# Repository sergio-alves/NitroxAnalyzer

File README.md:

# NitroxAnalyzer
This repository contains everything needed to build a nitrox analyzer that uses a compatible R17 O2 cell and that connects to a mobile phone running on Android.

The finished product:

Read [the wiki page](https://github.com/sergio-alves/NitroxAnalyzer/wiki) to get more information about the project.

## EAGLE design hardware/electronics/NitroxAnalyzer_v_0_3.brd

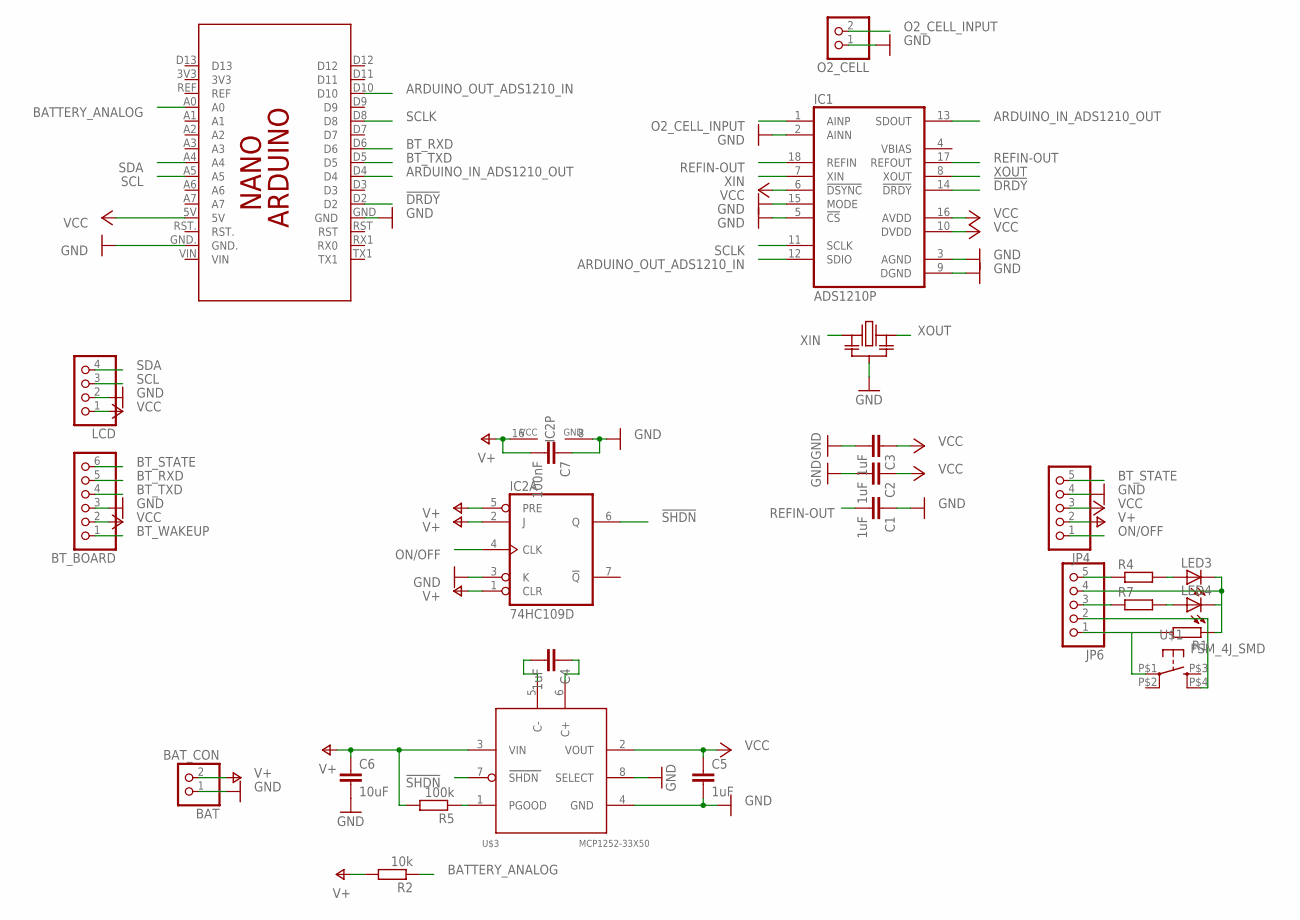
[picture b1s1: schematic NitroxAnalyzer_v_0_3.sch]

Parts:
BAT: BAT_CON; 1X02
BT_BOARD: PINHD-1X6; 1X06
C1, C2, C3, C4, C5: 1uF; C1206
C6: 10uF; C1206
C7: 100nF; C1206
IC1: ADS1210P; DIL18
IC2: 74HC109D; SO16
JP4: PINHD-1X5; 1X05
JP6: PINHD-1X5/90; 1X05/90
LCD: PINHD-1X4; 1X04
LED3, LED4: LEDSML0805; SML0805
O2_CELL: PINHD-1X2; 1X02
PCB1: ARDUINO_NANO_SOCKET
R1, R4, R7: R-EU_R1206; R1206
R2: 10k; R1206
R5: 100k; R1206
U$1: FSM_4J_SMD; B3F-10XX
U$2: RESONATOR
U$3: MCP1252-33X50; MSOP8

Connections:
!DRDY: IC1.14 (!DRDY), PCB1.D2
!SHDN: IC2.6 (Q), U$3.7 (SHDN)
ARDUINO_IN_ADS1210_OUT: IC1.13 (SDOUT), PCB1.D4
ARDUINO_OUT_ADS1210_IN: IC1.12 (SDIO), PCB1.D10
BATTERY_ANALOG: PCB1.A0, R2.1
BT_RXD: BT_BOARD.5, PCB1.D6
BT_STATE: BT_BOARD.6, JP4.5
BT_TXD: BT_BOARD.4, PCB1.D5
BT_WAKEUP: BT_BOARD.1
GND: BAT.1, BT_BOARD.3, C1.1, C2.2, C3.2, C5.2, C6.2, C7.1, IC1.2 (AINN), IC1.3 (AGND), IC1.5 (!CS), IC1.9 (DGND), IC1.15 (MODE), IC2.3 (K), IC2.8 (GND), JP4.4, LCD.2, O2_CELL.1, PCB1.GND, PCB1.GND., U$2.P$2 (GND), U$3.4 (GND), U$3.8 (SELECT)
unnamed: C4.1, U$3.6 (C+)
unnamed: R5.1, U$3.1 (PGOOD)
unnamed: LED3.A, R4.2
unnamed: LED4.A, R7.2
unnamed: C4.2, U$3.5 (C-)
O2_CELL_INPUT: IC1.1 (AINP), O2_CELL.2
ON/OFF: IC2.4 (CLK), JP4.1
REFIN-OUT: C1.2, IC1.17 (REFOUT), IC1.18 (REFIN)
SCL: LCD.3, PCB1.A5
SCLK: IC1.11 (SCLK), PCB1.D8
SDA: LCD.4, PCB1.A4
V+: BAT.2, C6.1, C7.2, IC2.1 (CLR), IC2.2 (J), IC2.5 (PRE), IC2.16 (VCC), JP4.2, R2.2, R5.2, U$3.3 (VIN)
VCC: BT_BOARD.2, C2.1, C3.1, C5.1, IC1.6 (!DSYNC), IC1.10 (DVDD), IC1.16 (AVDD), JP4.3, LCD.1, PCB1.5V, U$3.2 (VOUT)
XIN: IC1.7 (XIN), U$2.P$1 (IN)
XOUT: IC1.8 (XOUT), U$2.P$3 (OUT)
_BT_STATE: JP6.5, R4.1
_ON_OFF: JP6.1, R1.2, U$1.P$1
_V+: JP6.2, U$1.P$4 (S1)
_VCC: JP6.3, R7.1
__GND: JP6.4, LED3.C, LED4.C, R1.1

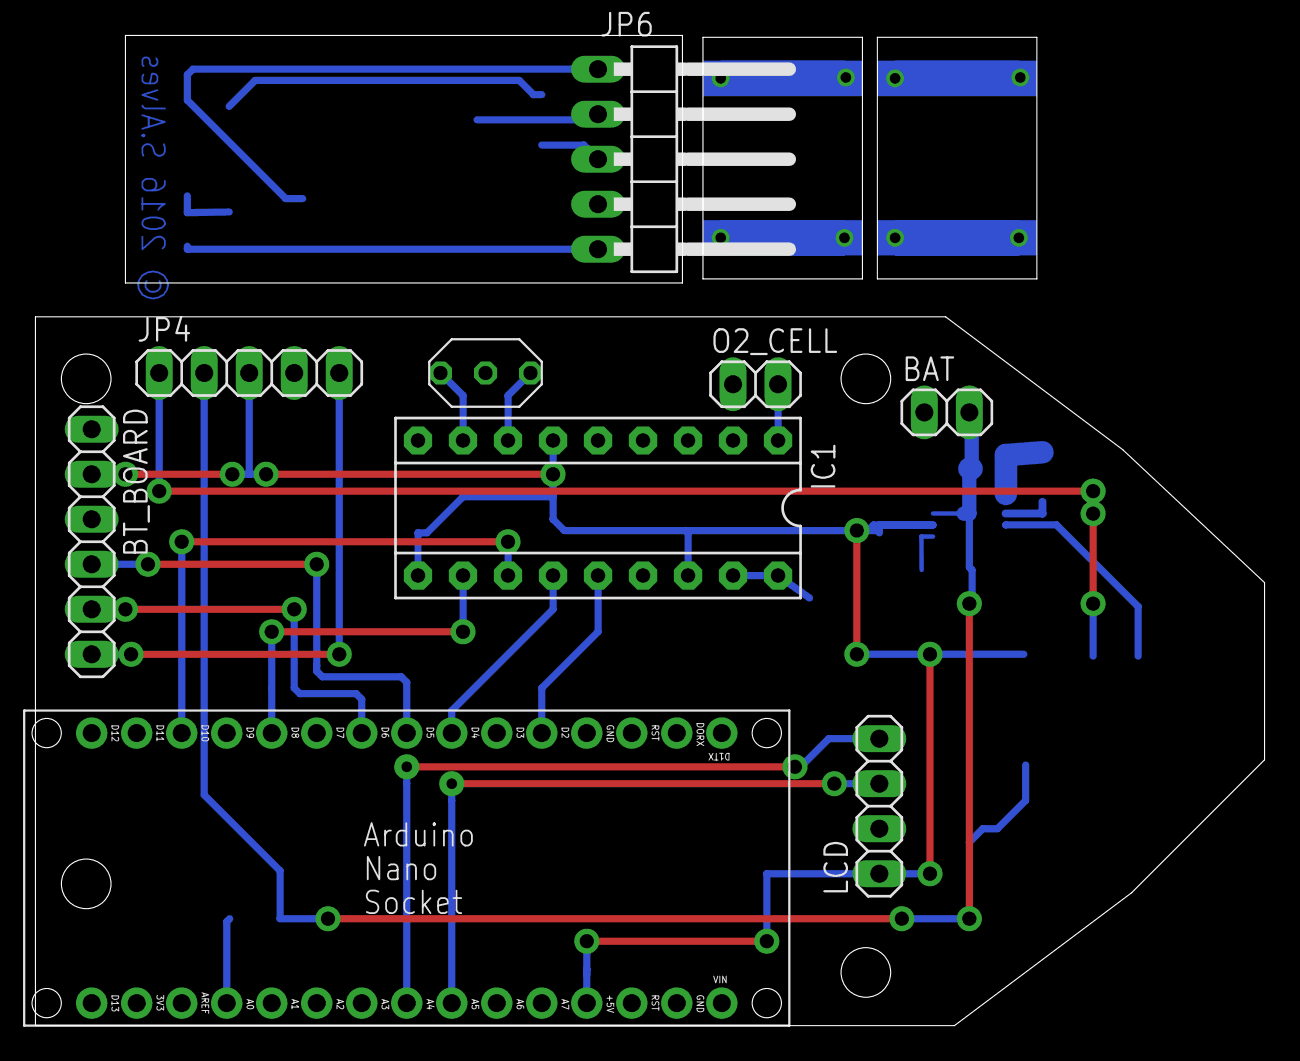
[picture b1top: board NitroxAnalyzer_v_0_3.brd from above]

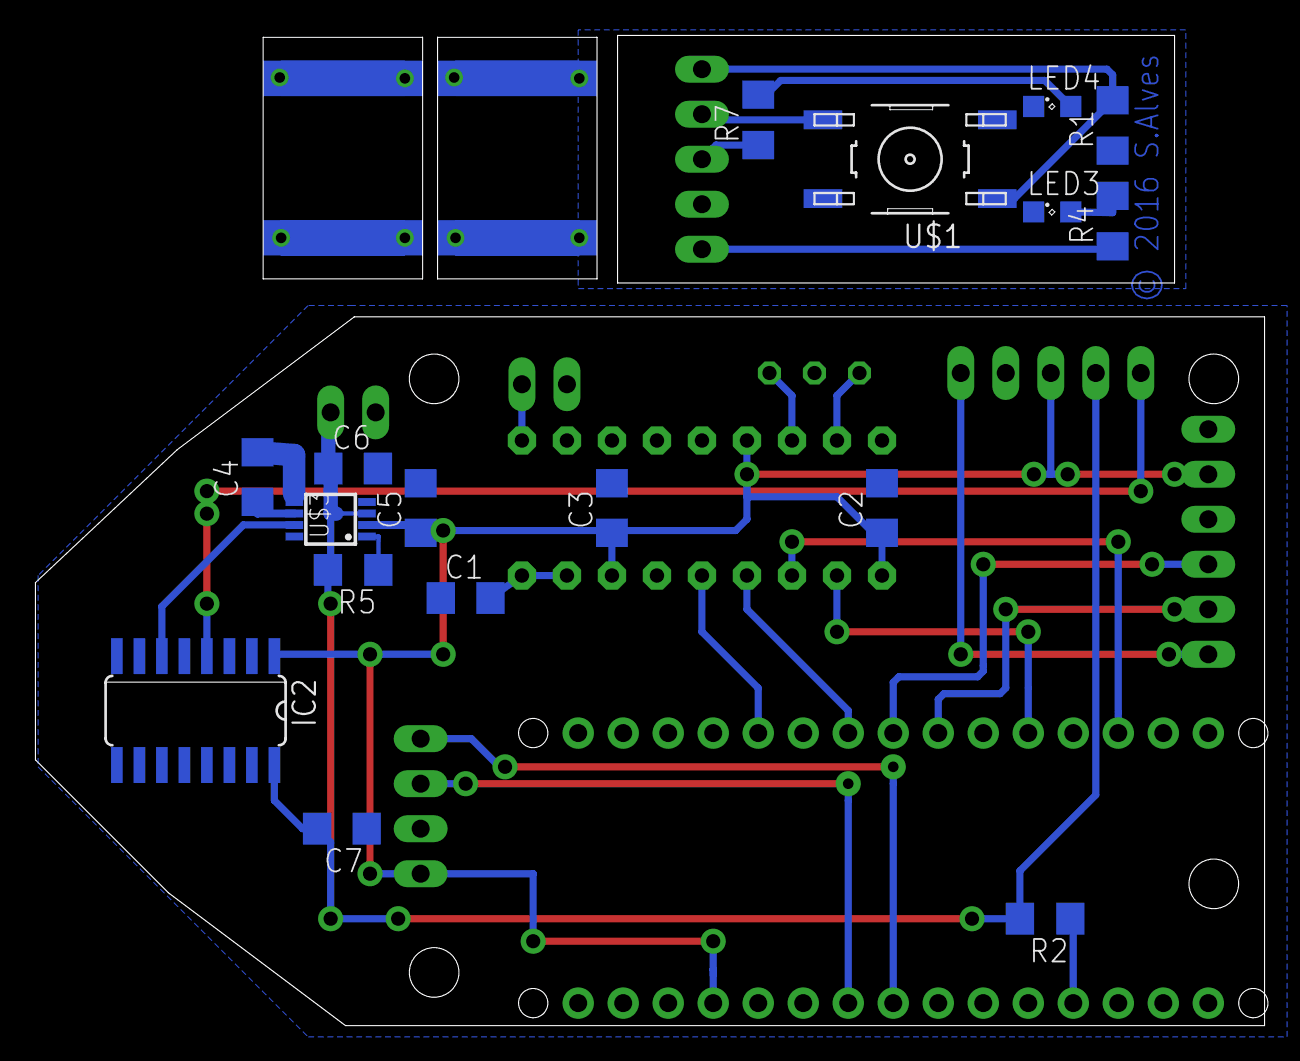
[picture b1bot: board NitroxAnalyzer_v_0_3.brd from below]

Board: 2 copper layers, 69.4 x 55.9 mm, 26 parts (17 on the bottom side), 29 nets.

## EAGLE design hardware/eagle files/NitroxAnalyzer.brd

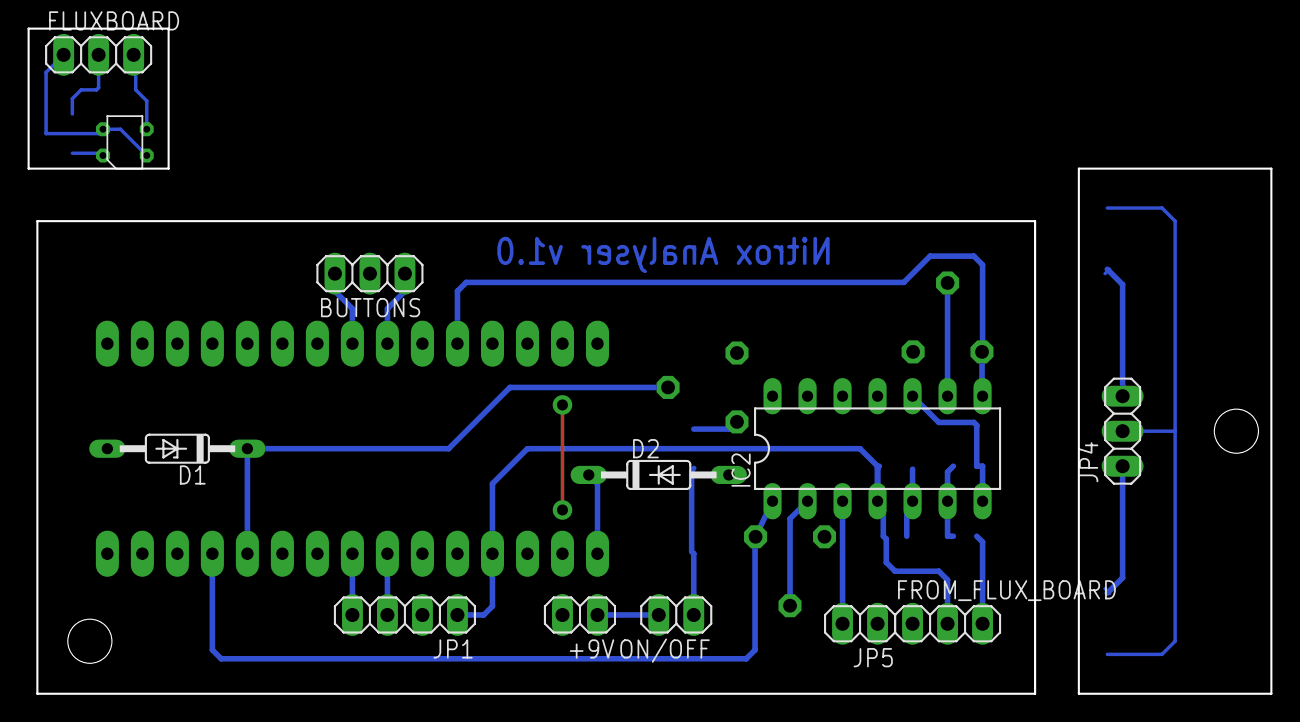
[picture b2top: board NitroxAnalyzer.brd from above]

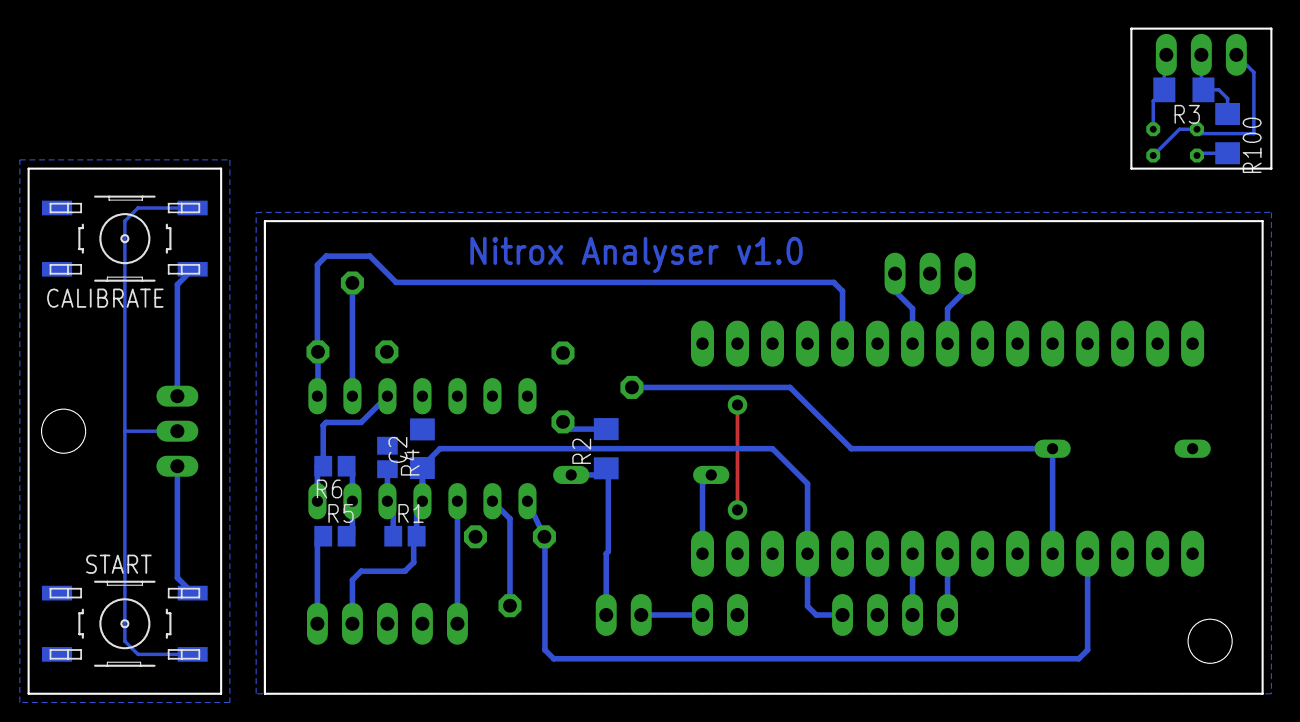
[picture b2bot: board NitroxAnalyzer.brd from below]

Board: 2 copper layers, 90.2 x 48.3 mm, 26 parts (10 on the bottom side), 27 nets.

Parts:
+9V: BAT_CON; 1X02
BUTTONS: 1X03
C2: 100n; C1206
CALIBRATE: FSM_4J_SMD; B3F-10XX
D1: BZX55; DO35Z10
D2: BA221; DO35-10
FLUXBOARD: 1X03
FROM_FLUX_BOARD: 1X03
IC2: LM2902N; DIL14
JP1: OLED_CON; 1X04
JP4: BUTTON_CON@2; 1X03
JP5: O2_CELL_CON; 1X02
ON/OFF: BAT_CON; 1X02
R1, R4, R5, R6: 91K; R0805
R2: 6K; R1206
R3: 10K; R1206
R100: 220; R1206
START: FSM_4J_SMD; B3F-10XX
U$1: 10K; PT6KV
U$2, U$5: 100K; PT6KV
U$3: 4PIN
U$4: DIL30

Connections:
+9V: D2.A, ON/OFF.1, R2.1
BATTERY_ANALOG: D1.C, U$1.C, U$4.P$20
CALIBRATE: BUTTONS.3, U$4.P$8
FLUX_DIGITAL: IC2.8, U$4.P$5, U$5.B
GND: +9V.2, BUTTONS.2, C2.2, D1.A, FROM_FLUX_BOARD.1, IC2.11, JP1.2, JP5.1, R4.1, U$1.B, U$2.A, U$4.P$4, U$4.P$29, U$5.A
GND_: FLUXBOARD.1, U$3.C, U$3.EMI
unnamed: R100.2, U$3.A
unnamed: IC2.2, U$2.C
unnamed: CALIBRATE.P$1, JP4.3
unnamed: +9V.1, ON/OFF.2
unnamed: JP4.1, START.P$2
unnamed: CALIBRATE.P$3, JP4.2, START.P$4
unnamed: D2.C, U$4.P$30
unnamed: R2.2, U$1.A
unnamed: IC2.7, IC2.10, R6.2
unnamed: IC2.6, R5.2, R6.1
unnamed: FROM_FLUX_BOARD.3, R5.1
unnamed: IC2.5, R1.1, R4.2
unnamed: IC2.9, U$5.C
unnamed: IC2.3, JP5.2
O2_CELL_ANALOG: IC2.1, U$2.B, U$4.P$19
SCL: JP1.3, U$4.P$24
SDA: JP1.4, U$4.P$23
SIG: FLUXBOARD.3, R3.2, U$3.COL
START: BUTTONS.1, U$4.P$7
VCC: C2.1, FROM_FLUX_BOARD.2, IC2.4, JP1.1, R1.2, U$4.P$27
VCC_: FLUXBOARD.2, R3.1, R100.1

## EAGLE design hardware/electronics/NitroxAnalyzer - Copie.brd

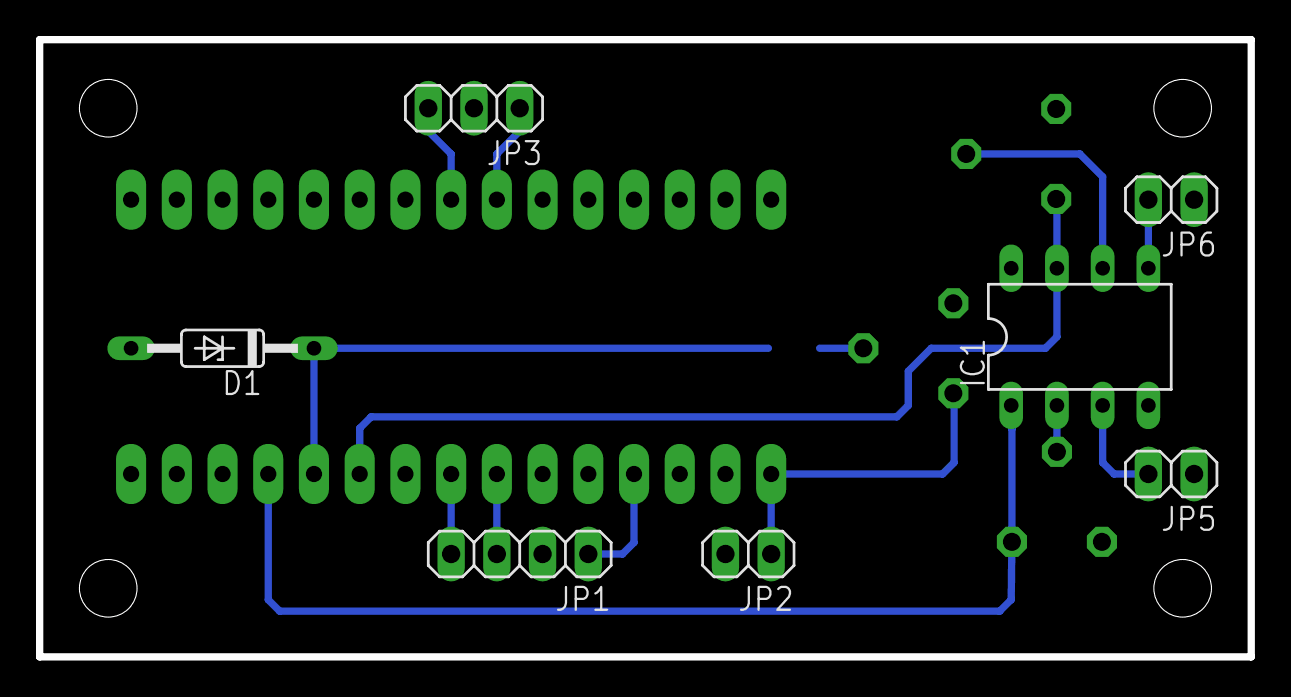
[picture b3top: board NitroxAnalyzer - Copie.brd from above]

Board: 2 copper layers, 67.3 x 34.3 mm, 12 parts (1 on the bottom side), 15 nets.

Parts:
D1: BZX55; DO35Z10
IC1: DIL08
JP1: OLED_CON; 1X04
JP2: BAT_CON; 1X02
JP3: BUTTONS_CON@1; 1X03
JP5: O2_CELL_CON; 1X02
JP6: FLUX_SENSOR_CON; 1X02
R1: 10k; R1206
U$1, U$2, U$3: PT6KV-10k; PT6KV
U$4: DIL30

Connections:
+9V: JP2.1, U$1.A, U$4.P$30
BATTERY_ANALOG: D1.C, R1.2, U$4.P$20
CALIBRATE: JP3.3, U$4.P$8
FLUX_ANALOG: IC1.7, U$3.A, U$4.P$21
FLUX_SIGNAL: IC1.5, JP6.2
GND: D1.A, JP1.2, JP2.2, JP3.2, JP5.1, JP6.1, U$1.B, U$2.B, U$3.B, U$4.P$4, U$4.P$29
unnamed: R1.1, U$1.C
unnamed: IC1.2, U$2.C
unnamed: IC1.6, U$3.C
O2_CELL_ANALOG: IC1.1, U$2.A, U$4.P$19
O2_SIGNAL: IC1.3, JP5.2
SCL: JP1.3, U$4.P$24
SDA: JP1.4, U$4.P$23
START: JP3.1, U$4.P$7
VCC: JP1.1, U$4.P$27

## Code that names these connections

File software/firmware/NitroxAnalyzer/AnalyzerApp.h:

#pragma once

#include <Arduino.h>
#include <EEPROM.h>
#include <SoftwareSerial.h>
#include <EEPROM.h>
#include <Wire.h>
#include <OzOLED.h>
#include "ADS1210Driver.h"
#include "OzOledDisplayAdapter.h"
#include "SerialProtocolHandler.h"
#include "Averager.h"


/*
enum ApplicationStates {

autoCalibrateAction,
autoMesuringAction,
refreshBatteryState,
refreshDataInOutState,
refreshBluetoothState,
displayBTConnectedScreen,
getBatteryLoad,
setO2CellInstallDate,
setO2CellValidityDate,
STATE_IDLE,
STATE_EXECUTE_GET_AVERAGE_INIT,
STATE_EXECUTE_GET_AVERAGE_READ_VALUES,
STATE_EXECUTE_GET_AVERAGE_RETURN_RESPONSE,
STATE_EXECUTE_GET_BATTERY_LOAD,
STATE_EXECUTE_GET_O2_CELL_INSTALL_DATE,
STATE_EXECUTE_SET_O2_CELL_INSTALL_DATE,
DISPLAY_SCREEN_ICONS,
};








*/

//----------------------------------------------------------------------------------------------------------
// Externals -----------------------------------------------------------------------------------------------
//----------------------------------------------------------------------------------------------------------
extern void adcIRQ();
class AnalyzerApp;

//----------------------------------------------------------------------------------------------------------
// Definitions ---------------------------------------------------------------------------------------------
//----------------------------------------------------------------------------------------------------------

#define isEEPROMClean() eeprom.configuration.clean==0xCAFEBABE

// pins related 

#define BATTERY_ANALOG_PIN				A0

#define ADS1210_CLK						8
#define ARDUINO_OUT_ADS1210_IN			10
#define ARDUINO_IN_ADS1210_OUT			4


//buttons related
#define LEFT_BUTTON						11
#define RIGHT_BUTTON					12

#define DEBOUNCE_MAX_MS					20

typedef struct {
	unsigned long lastUpdate;
	int currentState;
	void(AnalyzerApp::*onPush)(int);
	void(AnalyzerApp::*onRelease)(int);
	void(AnalyzerApp::*onPressed)(int, int);
} ButtonState;


// counters related
#define COUNTERS_SIZE					4

enum  Counters {
	mainCounter,
	bluetoothIcon,
	inOutCounter,
	bluetoothConnectionAlive,
};


//eeprom related 
#define EEPROM_STORED_DATA_SIZE			12
#define EEPROM_CONFIG_START_ADDRESS		0

typedef struct {
	int day;
	int month;
	int year;
} date;

typedef struct {
	long clean;
	struct {
		date install_date; //6 bytes
		date change_date;  //6 bytes
	} O2Cell; // 12 bytes
} AnalyzerConfiguration;

typedef union {
	byte data[sizeof(AnalyzerConfiguration)];
	AnalyzerConfiguration configuration;
} EEPROMContent;

//communication speed related
#define SOFTWARE_RX_PIN					5
#define SOFTWARE_TX_PIN					6

#define SERIAL_BAUDRATE					115200
#define BLUETOOTH_BAUDRATE				9600


// screens and loops related
#define SPLASH_SCREEN_DURATION_MS		2000

enum ScreenLoop {
	SplashScreen,
	ManualScreen,
	BluetoothScreen,
};
enum ApplicationStates {
	idle,
	wait,
	calibrate,
	measure,
	displaySplashScreen,
	displayMainScreen,

	getO2CellInstallDate,
	getO2CellValidityDate,
};

enum DataInOutState{
	none,
	in,
	out,
	inout,
};

/* Calibration related */
#define CALIBRATION_MAX_ITERATIONS  100
#define O2_READ_ITERATIONS			10


/* Class to handle the analyzer application.
   Calibration and measures can be done using the box or through the bt interface (if available)
   then the structure must be rather flexible.
   On BT Connection device will answer to bt commands only, no device interaction possible. */
class AnalyzerApp
{
public:
	void doLoop();
	void doSetup();
	inline void setNewADCValueAvailable(bool val) { newADCValueAvailable = val; }

protected:
	/* button events related functions */
	void onButtonPressed(int btnId, int length);
	void onButtonRelease(int btnId);
	void onButtonPush(int btnId);
	void poolButtonsState();
	bool stateChangedDebounced(int);

	/* sub loops related */
	ScreenLoop splashScreenLoop();
	ScreenLoop manualScreenLoop();
	ScreenLoop bluetoothScreenLoop();

	/* displaying related*/
	void drawsManualMainScreen();
	int getBatteryPercent();
	int getBatteryMappedValue();
	void inOutIconUpdate(bool send, bool receive);
	void convertDecimalToDigits(long decval);
	long fromIntToDigitsArray(int digit, long decvalcp, long power);

	/* bluetooth serial communication related */
	ApplicationStates getNextCommand(ApplicationStates current);

	/* eeprom related */
	void loadConfigurationFromEEPROM();

	/* manual octions related*/
	ApplicationStates doCalibration(ApplicationStates current, ApplicationStates next);
	ApplicationStates doO2Measure(ApplicationStates current, ApplicationStates next);


private:
	SoftwareSerial BTSerial = SoftwareSerial(SOFTWARE_RX_PIN, SOFTWARE_TX_PIN);
	SerialProtocolHandler protocolHandler = SerialProtocolHandler(BTSerial);
	EEPROMContent eeprom;
	ApplicationStates applicationState;
	ButtonState buttons[2];
	bool btConnection = false;
	ScreenLoop currentLoop = SplashScreen;
	unsigned long counters[COUNTERS_SIZE];
	bool newADCValueAvailable = false;
	bool autoCalibrate = true;
	bool autoMeasure = true;
	DataInOutState dataInOutState = none;
	int bluetoothState = 0;
	SerialCommand * command;
	int subFunctionState = 0;
	Averager averager;
	double average,  oldAverage;
	byte displayDigits[9];
	long calibrationValue = 0;
	char buffer[128];



	/*
protected:
	void bluetoothDoLoop();
	void screenDisplayLoop();
	bool dataInOutChanged();
	bool bluetoothStateChanged();
	bool batteryStateChanged();
private:	
	DataInOutState oldDataInOutState = none;
	int oldBluetoothState = 0;
	int batteryState = 0;
	int oldBatteryState = 0;
	ApplicationStates screenDisplayState = idle;
	ApplicationStates bluetoothApplicationStates = idle;
	int counter = 0, iterations=0;
	unsigned long average = 0;
	long min = 0x7FFFFFFF, max = 0x80000000;
	bool numDigitFound = false;
	SendingBuffer sb;
	DWORD_MAX_187_DATA_FORMAT current;
	
	char c;
	
	int maxIterations = 10;*/
};

extern AnalyzerApp app;

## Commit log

2015-11-25 First iteration for the nitrox analyzer.
    There is a first version for :
    - The box (freecad file)
    - The firmware (arduino file)
    - The hardware (eagle file)
    And a helper project used to convert pbm files into a byte array convenient to api used to communicate with the ssd1306 display controller
2015-11-25 all the stuff to be ignored
2015-11-25 added some pictures to resources
2015-11-25 added basic firmware flowchart to resources
2015-11-27 Did a bit of refactoring to the firmware.
    Separated the display functions from the control functions, it's not perfect but clearly better than before. I'll continue with some refactoring more
2015-11-27 The arduino library to communicate with my OLED screen.
2015-11-27 Updated a bit the buttons hardware board to better match the 3d box
2015-11-27 some files to be ignored
2015-11-27 The fittings connector that will direct the nitrox flux from the tank to the analyzer
2015-11-27 updated the markdown page to direct people to the wiki
2015-11-27 Updated the Code to decouple the AnalyzerApp from the screen driver
2015-11-27 Cleaned AnalyzerApp
2015-11-28 Updated some 3d cad models and other stuff
2016-01-08 last commit on this solution.
    I got some drawbacks that force to change the approach.
    1- No more screen and buttons but an Android interface
    2- Bluetooth Connection will be used
2016-01-24 - moved android app to the project
    - refactored android app
    - added box v2
    - added circuit v2 that fits box v2
    - added presentation of the project
2016-01-24 moved projects
2016-01-24 ignored files
2016-01-24 moving files + exported 3D parts for the box
2016-01-24 added some new images
2016-01-24 added images of schematic and board
2016-01-24 added new image
2016-01-24 Delete NitroxAnalyzer.sch
    doen't need it anymore
2016-01-24 Delete NitroxAnalyzer.brd
    doen't need it anymore
2016-01-24 doen't need it anymore
2016-01-24 Delete NitroxAnalyzer - Copie.brd
    doen't need it anymore
2016-01-24 Delete FSM_4J.lbr
    doen't need it anymore
2016-01-24 Delete ITR8307.lbr
    doen't need it anymore
2016-01-24 Delete piher.lbr
    doen't need it anymore
2016-01-25 Added small presentation
2016-01-25 fixed small bug when app lose connection
2016-01-26 changes in project
2016-01-26 Created a version of the box with an aperture for an LCD
2016-01-27 version with screen on top of box
    Screen type i2c
    Supply Voltage :5V
    Unterstützt I2C Protokoll
    Auflösung 128X64
    Packetinhalt:
    1) 1 x I2C OLED 0.96 inch
2016-02-04 Created new box and new electro circuit that adds lcd connection
2016-05-31 updated firmware to display o2 rate. Need to update the android app

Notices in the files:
hardware/electronics/NitroxAnalyzer_v_0_3.brd:
© 2016 Sergio Alves
All rights reserved
© 2016 S.Alves
